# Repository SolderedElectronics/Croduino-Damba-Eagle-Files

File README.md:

# Croduino Damba Eagle Files
## Image

[Croduino Damba(100016)](https://e-radionica.com/en/croduino-damba.html)

## Description and details
The Croduino Damba is a very small Arduino compatible board. It is sized just 22 x 26 mm (0.9 x 1 inch) and features a CR1220 battery onboard so it easily becomes a wearable. It is based on Attiny85 microcontroller which runs an Arduino bootloader.

To program this board you will need another Arduino board. The process of programming is made simple since there is a connector on Damba for plugging in directly in Arduino board (for example, Croduino Basic).

###More specs:
- Size: 22 x 26 mm
- Attiny85 microcontroller on board features 6 digital outputs of which are 2 PWM, 4 analog input and possibility for SPI or I2C communication
- Embedded 1MHz or 8MHz oscillator with possibility to connect external one, up to 20MHz
- Works from 2.7V to 5.5V
- Has CR1220 battery socket on its back to make it full-featured wearable
- Orange LED on D0 pin, easy to disable it by desoldering/cutting trace
- Simple programming
- 6.5kB available in Flash, 0.5kB SRAM, 0.5kB EEPROM
- Free lifetime technical support at techsupport@e-radionica.com
- Made in EU (Croatia)

## Repository content
This repo contains Cadsoft Eagle .sch and .brd files for Croduino Damba board. It also contains schematic in .pdf created from .sch Eagle file. 
Files have been arranged into folders for navigating between different versions of board. 
Tip: layer 200 shows top silkscreen and layer 208 should be bottom silkscreen. tParts and bParts is not used.

## Docs
- [Croduino Damba product page] (https://e-radionica.com/en/croduino-damba.html)

## Board versions
- v1.0 - inital version

## License info
This product is open-source. Yay!
For any tech questions, contact us at techsupport@e-radionica.com
If you find an Issue, please open one at GitHub. If you can improve our product, fork us.

e-radionica.com Team.

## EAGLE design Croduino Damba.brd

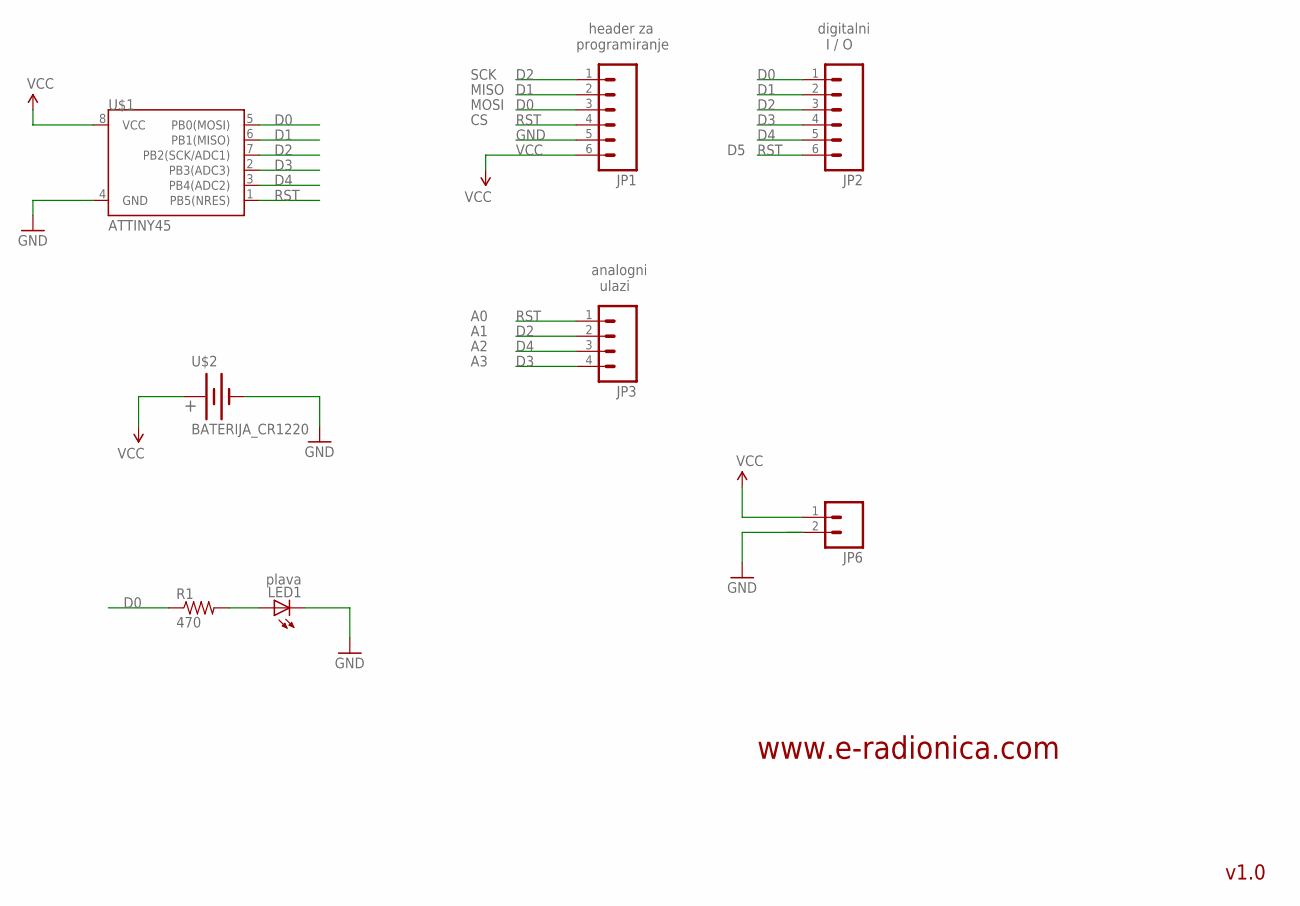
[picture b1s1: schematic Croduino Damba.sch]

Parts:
JP1, JP2: M06SIP; 1X06
JP3: M04PTH; 1X04
JP6: M02PTH; 1X02
LED1: plava; CHIPLED_0805
R1: 470; 0603-RES
U$1: ATTINY45; SO08-EIAJ
U$2: BATERIJA_CR1220; BATERIJA12MM

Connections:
D0: JP1.3, JP2.1, R1.1, U$1.5 (PB0(MOSI))
D1: JP1.2, JP2.2, U$1.6 (PB1(MISO))
D2: JP1.1, JP2.3, JP3.2, U$1.7 (PB2(SCK/ADC1))
D3: JP2.4, JP3.4, U$1.2 (PB3(ADC3))
D4: JP2.5, JP3.3, U$1.3 (PB4(ADC2))
GND: JP1.5, JP6.2, LED1.C, U$1.4 (GND), U$2.-
unnamed: LED1.A, R1.2
RST: JP1.4, JP2.6, JP3.1, U$1.1 (PB5(NRES))
VCC: JP1.6, JP6.1, U$1.8 (VCC), U$2.+

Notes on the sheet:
header za programiranje
SCK
MISO
MOSI
digitalni I / O
analogni ulazi
v1.0
www.e-radionica.com

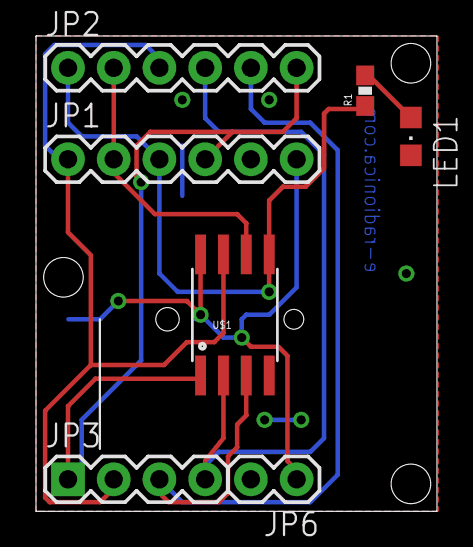
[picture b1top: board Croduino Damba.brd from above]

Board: 2 copper layers, 22.3 x 26.4 mm, 11 parts (0 on the bottom side), 9 nets.

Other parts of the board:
U$3: UTICNICA3MM
U$4: OSH3MM
U$5: DAMBA

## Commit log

2015-08-14 Adding files
2015-08-24 Write Readme, add version folder
2016-02-12 README change
    Changed links on e-radionica.com from HTTP to HTTPS since we enabled
    SSL.
2018-11-26 README update

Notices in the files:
parts and their libraries:
SparkFun: Licensing: CC v3.0 Share-Alike You are welcome to use this library for commercial purposes.
